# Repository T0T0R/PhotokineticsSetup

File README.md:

# PhotokineticsSetup
A microcontroller (STM32F103C8) drives at the same time an Hamamatsu lamp through its RS232 interface, and two flip mounts MFF101 via TTL inputs.

## Installation
This script works with Python 3.9.
The pySerial library must be installed in order to achieve serial communication with the microcontroler. This can be done by typing the following command in the system console:
```
python -m pip install pyserial
```
The Tkinter GUI is used in this program. There shouldn't be any need to install it since it is an integral part of most of Python installations.

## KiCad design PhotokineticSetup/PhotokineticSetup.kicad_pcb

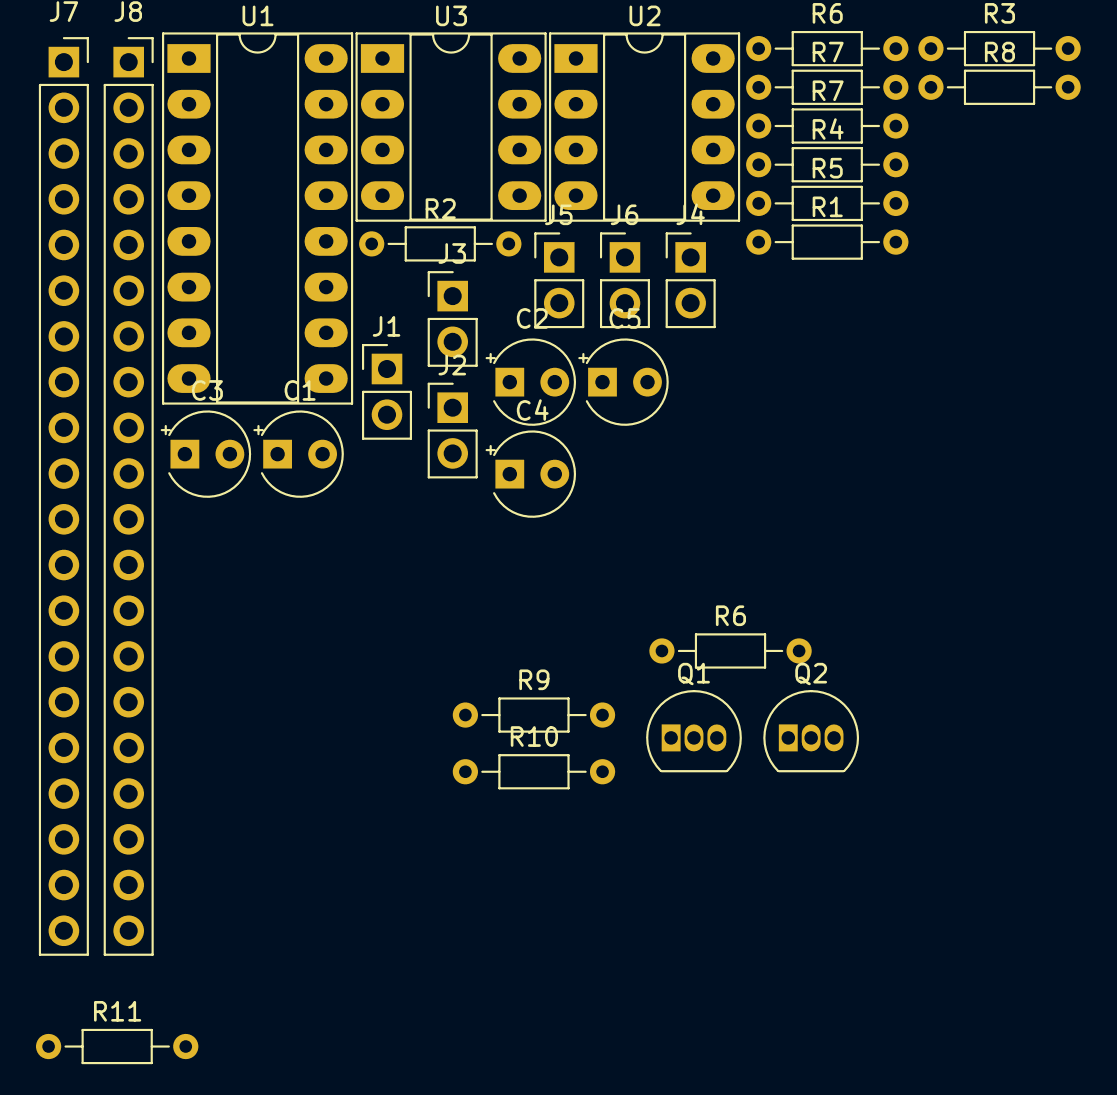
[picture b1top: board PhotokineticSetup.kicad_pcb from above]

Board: 2 copper layers, 31 parts (0 on the bottom side), 35 nets, no tracks yet.

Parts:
C1, C2, C3, C4, C5: 1u; CP_Radial_Tantal_D4.5mm_P2.50mm
J1: Conn_01x02; PinHeader_1x02_P2.54mm_Vertical
J2: Serial; PinHeader_1x02_P2.54mm_Vertical
J3: LEDs; PinHeader_1x02_P2.54mm_Vertical
J4: Switches; PinHeader_1x02_P2.54mm_Vertical
J5: Outputs; PinHeader_1x02_P2.54mm_Vertical
J6: Inputs; PinHeader_1x02_P2.54mm_Vertical
J7, J8: Conn_01x20; PinSocket_1x20_P2.54mm_Vertical
Q1, Q2: 2N3904; TO-92_Inline
R1: 82; R_Axial_DIN0204_L3.6mm_D1.6mm_P7.62mm_Horizontal
R2, R11: 68; R_Axial_DIN0204_L3.6mm_D1.6mm_P7.62mm_Horizontal
R3, R4: 270; R_Axial_DIN0204_L3.6mm_D1.6mm_P7.62mm_Horizontal
R5, R6, R9, R10: 1k; R_Axial_DIN0204_L3.6mm_D1.6mm_P7.62mm_Horizontal
R6#2, R7: 10k; R_Axial_DIN0204_L3.6mm_D1.6mm_P7.62mm_Horizontal
R7#2, R8: 470; R_Axial_DIN0204_L3.6mm_D1.6mm_P7.62mm_Horizontal
U1: MAX232; DIP-16_W7.62mm_Socket_LongPads
U2, U3: ILD615; DIP-8_W7.62mm_Socket_LongPads

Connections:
+3V3: J1.1, J8.3, R5.1, R6.1, R11.2, U3.1, U3.4, U3.6, U3.7
+5V: C5.1, J7.18, U1.16
/PA0: J8.16, U3.5
/PA1: J8.15, U3.8
/PA2: J8.14, U1.10
/PA3: J8.13, U1.9
/PA4: J8.12, R2.2
/PA7: J8.9, R1.2
/PA8: J7.5, R3.1
/PA9: J7.6, R4.1
/PB10: J8.6, U1.11
/PB11: J8.5, U1.12
/PB14: J4.1, J7.3
/PB15: J4.2, J7.4
GND: C3.2, C4.1, C5.2, J1.2, J7.19, J8.1, J8.2, R6#2.2, R7.2, R7#2.2, R8.2, U1.15, U2.2, U2.3, U2.5, U2.8
unnamed: C1.1, U1.1
unnamed: C1.2, U1.3
unnamed: C2.1, U1.4
unnamed: C2.2, U1.5
unnamed: C3.1, U1.2
unnamed: C4.2, U1.6
unnamed: J2.1, U1.14
unnamed: J2.2, U1.13
unnamed: J3.1, R1.1
unnamed: J3.2, R2.1
unnamed: J5.1, R5.2, R6#2.1, U2.7
unnamed: J5.2, R6.2, R7.1, U2.6
unnamed: J6.1, Q1.2, R9.1
unnamed: J6.2, Q2.2, R10.1
unnamed: Q1.1, R7#2.1
unnamed: Q1.3, U3.2
unnamed: Q2.1, R8.1
unnamed: Q2.3, U3.3
unnamed: R3.2, U2.1
unnamed: R4.2, U2.4

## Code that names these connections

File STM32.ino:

/* Start: April 2021
 *  Interface Serial console / Hamamatsu lamp & motors
 *  UART and RS-232 protocol
 *  Last modification: 11/06/2021
 */

#define FILTERA PA8 // Pin used to drive filter A.
#define FA_IS_MOVING PA0     // Pin used to receive the feedback from filter A (LOW if the filter is locked in position).
#define FILTERB PA9 // Pin used to drive filter B.
#define FB_IS_MOVING PA1     // Pin used to receive the feedback from filter B (LOW if the filter is locked in position).

#define SWITCHA PB14  // Switch controlling the position of filter A in manual mode.
#define SWITCHB PB15  // Switch controlling the position of filter B in manual mode.

#define LED_MOTORS PA4  // LED indicating the mechanical activity of filters.
#define LED_MANUAL PA7    // LED indicating that the manual mode is active.


HardwareSerial Serial3(PB11, PB10); // Enables UART communication through serial3 ports (RX3=PB11, TX3=PB10).
//HardwareSerial Serial2(PA3, PA2);


String computerStr = "";  // Stores the message from the computer.
String lampStr = "";      // Stores the message from the lamp.

/*  When manual mode is activated, the computer's instructions to drive filters will be ignored by the microcontroller.
 * Instead, it will drive them accordingly to states of SWITCHA and SWITCHB.
 * When the power is turned on, the default behavior is manual because you may not want to connect the computer to just move a filter.
 */
bool manualMode = true;







/*  This function toggles the state of FILTERA and FILTERB  in order to move the connected filters.
 * A LOW signal will switch it to position POS1, ad HIGH to POS2. 
 */
void moveFilter(byte const& filter, byte pos){
  pos = ((pos-1)%2 )+1; // Make sure that the requested position is between 1 and 2.
  
  int filterPin = 0;
  if (filter==1){
    filterPin = FILTERA;
  }else if (filter==2){
    filterPin = FILTERB;
  }

  digitalWrite(LED_MOTORS, HIGH);
  
  if(pos == 1) digitalWrite(filterPin, LOW);
  else digitalWrite(filterPin, HIGH);

  while (digitalRead(FA_IS_MOVING) || digitalRead(FB_IS_MOVING)) continue;  // Wait until the filter stops moving

  digitalWrite(LED_MOTORS, LOW);

  if (filter==1){
    Serial.write("FAOK\r");
  }else if (filter==2){
    Serial.write("FBOK\r");
  }
}










void setup(){
  Serial.begin(9600, SERIAL_8N1);   // Communication with the computer: 9600 bauds, 8 data bits, no parity, one stop bit.
  Serial3.begin(9600, SERIAL_8N1);  // Communication with the Hamamatsu lamp: 9600 bauds, 8 data bits, no parity, one stop bit.
  delay(1000);
  
  pinMode(LED_BUILTIN, OUTPUT);
  pinMode(FILTERA, OUTPUT);  digitalWrite(FILTERA, LOW);
  pinMode(FILTERB, OUTPUT); digitalWrite(FILTERB, LOW);

  pinMode(FA_IS_MOVING, INPUT_PULLDOWN); // If feedback is not connected, filters will be seen as not moving by the microcontroller and so it will not wait for them to stop moving.
  pinMode(FB_IS_MOVING, INPUT_PULLDOWN);
  pinMode(SWITCHA, INPUT_PULLDOWN);
  pinMode(SWITCHB, INPUT_PULLDOWN);

  pinMode(LED_MOTORS, OUTPUT);  digitalWrite(LED_MOTORS, LOW);
  pinMode(LED_MANUAL, OUTPUT);  digitalWrite(LED_MANUAL, LOW); 
}






void loop(){
  digitalWrite(LED_BUILTIN, HIGH); // Turn off the LED monitoring the serial transmission.
  

  if(Serial.available()){
    digitalWrite(LED_BUILTIN, LOW);  // Turn on the LED monitoring the serial transmission.
    
    computerStr = Serial.readStringUntil('\r')+'\r'; // Captures the incoming instruction (ending with the '\r' character).

    if(computerStr=="MOVA1\r" && (not manualMode)){  // Check if the received instruction is concerning the filters or the lamp.
      moveFilter(1,1);
    }else if(computerStr=="MOVA2\r" && (not manualMode))  moveFilter(1,2);
    else if(computerStr=="MOVB1\r" && (not manualMode))   moveFilter(2,1);
    else if(computerStr=="MOVB2\r" && (not manualMode))   moveFilter(2,2);
    else if(computerStr=="MAN1\r"){
      manualMode = false;
      Serial.write("MAN1OK\r");
    }
    else if(computerStr=="MAN2\r"){
      manualMode = true;
      Serial.write("MAN2OK\r");
    }
    else{  // If the received instructions do not concern filters, they are passed to the lamp.

      char* buf = (char*) malloc(sizeof(char)*(computerStr.length() + 1)); // Creates a char array buffer to store the string $computerStr$.
      computerStr.toCharArray(buf, computerStr.length() + 1);              // Convert String $computerStr$ to a char array $cString$.

      while (digitalRead(FA_IS_MOVING) || digitalRead(FB_IS_MOVING)) continue;  // If a filter is moving, wait until it stops to send instructions to the lamp. 
      
      Serial3.write(buf);
      free(buf);
        
    }
  }



  if (manualMode){  // In manual mode, check states of switches to drive filters.
    digitalWrite(LED_MANUAL, HIGH);
    digitalWrite(FILTERA, digitalRead(SWITCHA));
    digitalWrite(FILTERB, digitalRead(SWITCHB));
  }else{
    digitalWrite(LED_MANUAL, LOW);
  }
  

 
  //  Transmits messages from the lamp to the computer.
  while(Serial3.available()){
    digitalWrite(LED_BUILTIN, LOW);  // Turn on the LED monitoring the serial transmission.
    Serial.write(Serial3.read());
  }

delay(10);
}

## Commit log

2021-06-14 First sommit
2021-06-14 Add schematic diagrams
2021-06-16 Clearer optocouplers outputs and stronger input
2021-06-16 LED resistors calculated according to forward voltage
2021-06-20 Missing GND node + better placement of R7 & R8
2021-06-20 All serial communications at 9600 bauds.
2021-11-18 Threading of the irradiation methods. Keeps a log file.
2021-11-18 Mask layer for the PCB
2021-11-18 Bug fixes.
    Sequence can be started after testing an irradiation step of toggling the manual mode off.
2021-11-18 Correct naming of outputs.
2021-11-25 Removal of a duplicate.
